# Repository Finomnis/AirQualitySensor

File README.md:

# AirQualitySensor

-- in development --

> **IMPORTANT**
>
> This project will most likely never be released in a way that it can be replicated by other makers.
> It is a repository for personal use only.
> 
> I kind of finished the project but didn't actually manufacture a dedicated PCB for it. Therefore there
> are no official schematics for the hardware.
>
> Note that the `v1` hardware that I did get manufactured had an unknown error in it that kept messing up the calibration of the Senseair S8 in random intervals. I never found out what the problem was.

---

Simple Air Quality sensor based on:

-   nRF52840 (Microcontroller + Zigbee)
-   Senseair S8 (CO2)
-   AM2302/DHT22 (Temperature + Humidity)
-   Zigbee (SmartHome Connectivity)
-   DOGM132W-5 (Display)
-   uGFX (UI)

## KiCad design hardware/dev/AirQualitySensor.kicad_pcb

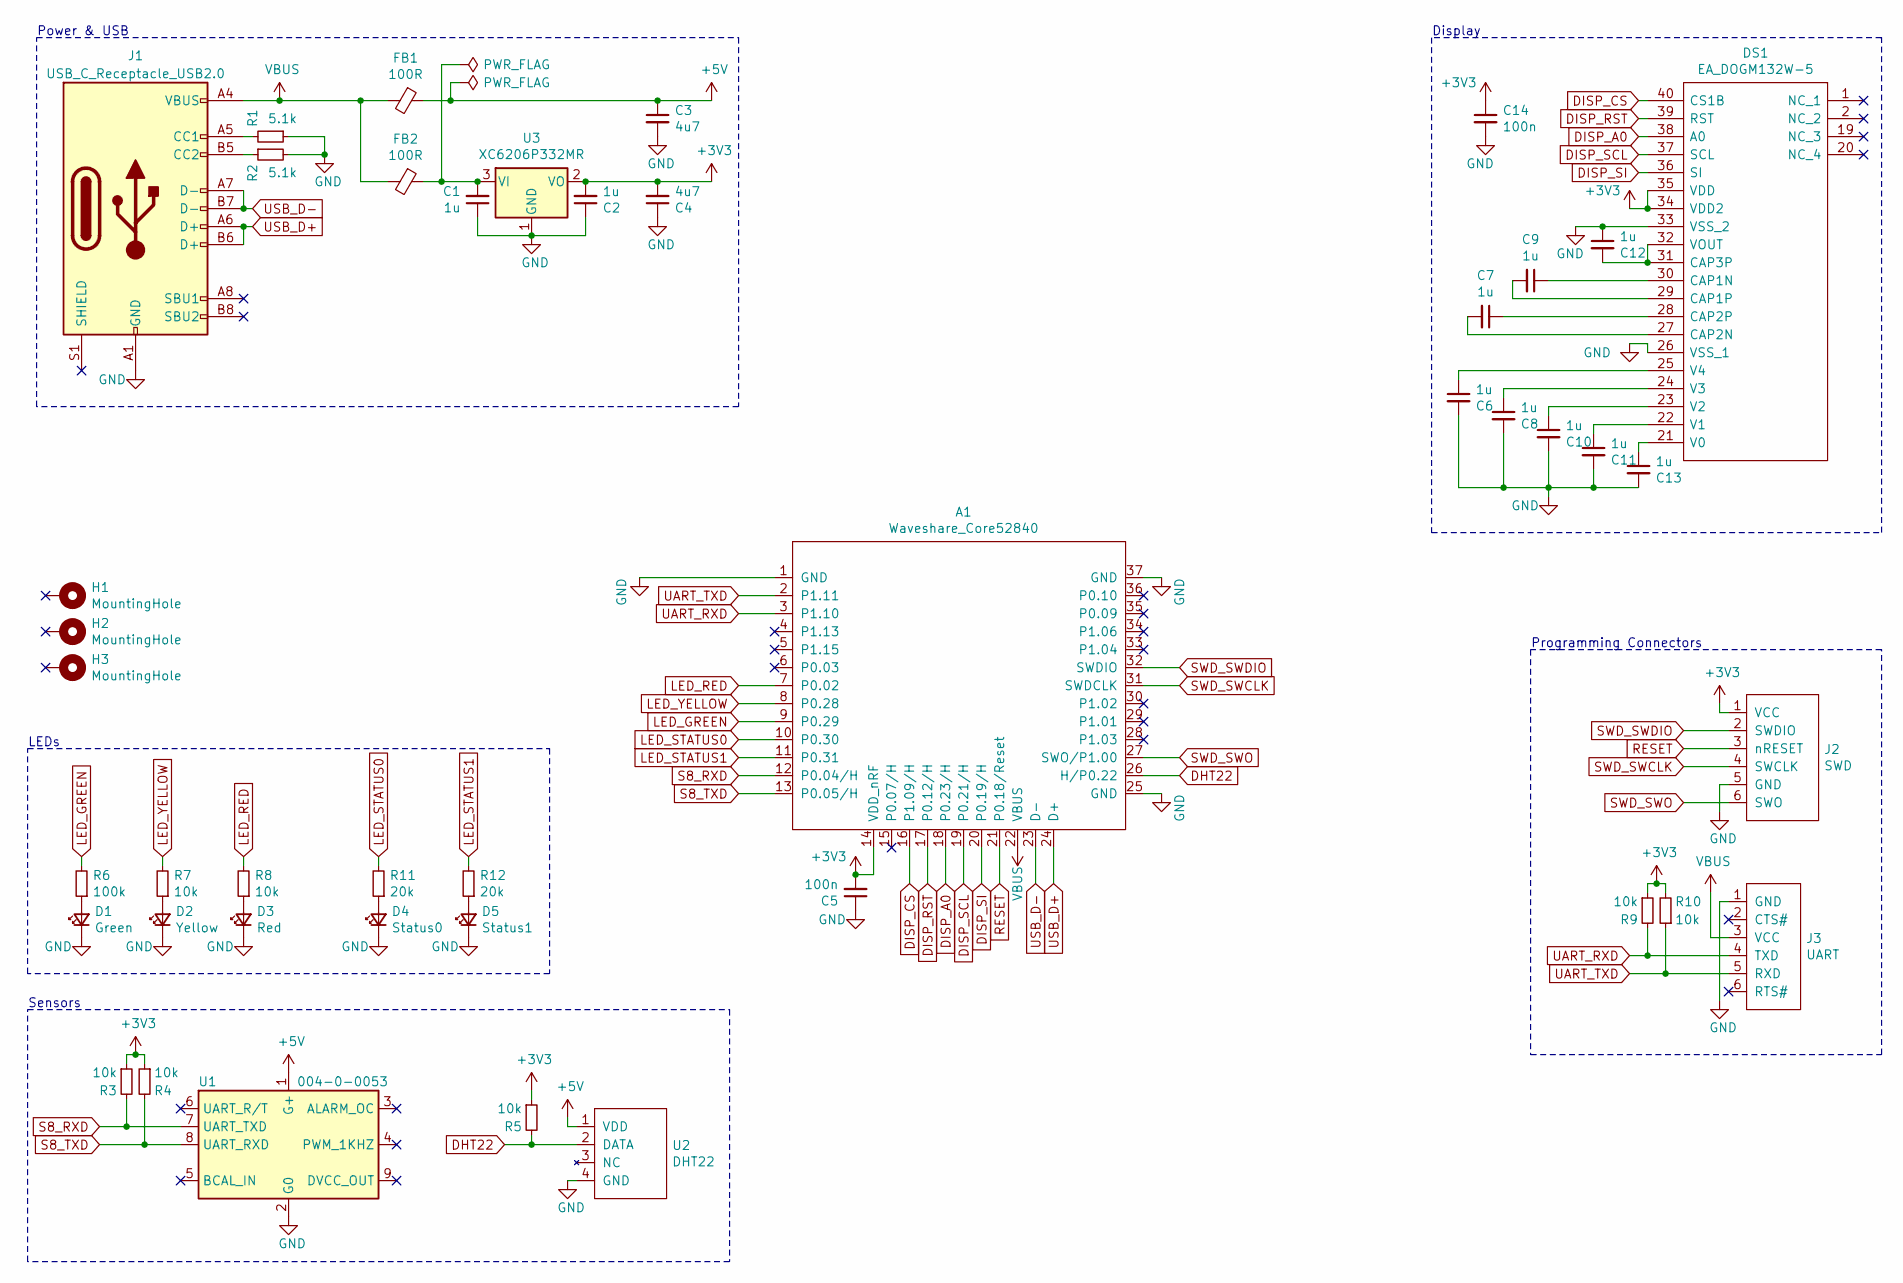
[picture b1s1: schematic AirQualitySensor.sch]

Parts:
A1: Waveshare_Core52840
C1, C2: 1u; C_0603_1608Metric
C3, C4: 4u7; C_0603_1608Metric
C5, C14: 100n; C_0402_1005Metric
C6, C7, C8, C9, C10, C11, C12, C13: 1u; C_0402_1005Metric
D1: Green; LED_D3.0mm
D2: Yellow; LED_D3.0mm
D3: Red; LED_D3.0mm
D4: Status0; LED_0805_2012Metric
D5: Status1; LED_0805_2012Metric
DS1: EA_DOGM132W-5; Mouser Part Number 790-EADOGM132W5
FB1, FB2: 100R; L_0805_2012Metric_Pad1.15x1.40mm_HandSolder
H1, H2, H3: MountingHole; MountingHole_2.5mm_Pad
J1: USB_C_Receptacle_USB2.0; USB_C_Receptacle_HRO_TYPE-C-31-M-12
J2: SWD; TC2030-IDC-FP
J3: UART; PinHeader_1x06_P2.54mm_Vertical
R1, R2: 5.1k; R_0402_1005Metric
R3, R4, R5, R7, R8, R9, R10: 10k; R_0402_1005Metric
R6: 100k; R_0402_1005Metric
R11, R12: 20k; R_0402_1005Metric
U1: 004-0-0053; Senseair_S8_Up
U2: DHT22
U3: XC6206P332MR; SOT-23

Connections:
+3V3: A1.14 (VDD_nRF), C2.2, C4.2, C5.2, C14.1, DS1.34 (VDD2), DS1.35 (VDD), J2.1 (VCC), R3.1, R4.1, R5.1, R9.1, R10.2, U3.2 (VO)
+5V: C3.1, FB1.1, U1.1 (G+), U2.1 (VDD)
DHT22: A1.26 (H/P0.22), R5.2, U2.2 (DATA)
DISP_A0: A1.18 (P0.23/H), DS1.38 (A0)
DISP_CS: A1.16 (P1.09/H), DS1.40 (CS1B)
DISP_RST: A1.17 (P0.12/H), DS1.39 (RST)
DISP_SCL: A1.19 (P0.21/H), DS1.37 (SCL)
DISP_SI: A1.20 (P0.19/H), DS1.36 (SI)
GND: A1.1 (GND), A1.25 (GND), A1.37 (GND), C1.1, C2.1, C3.2, C4.1, C5.1, C6.2, C8.2, C10.2, C11.2, C12.1, C13.2, C14.2, D1.1 (K), D2.1 (K), D3.1 (K), D4.1 (K), D5.1 (K), DS1.26 (VSS_1), DS1.33 (VSS_2), J1.A1 (GND), J1.A12 (GND), J1.B1 (GND), J1.B12 (GND), J2.5 (GND), J3.1 (GND), R1.1, R2.2, U1.2 (G0), U2.4 (GND), U3.1 (GND)
LED_GREEN: A1.9 (P0.29), R6.2
LED_RED: A1.7 (P0.02), R8.2
LED_STATUS0: A1.10 (P0.30), R11.2
LED_STATUS1: A1.11 (P0.31), R12.2
LED_YELLOW: A1.8 (P0.28), R7.2
unnamed: C1.2, FB2.1, U3.3 (VI)
unnamed: C6.1, DS1.25 (V4)
unnamed: C7.1, DS1.28 (CAP2P)
unnamed: C7.2, DS1.27 (CAP2N)
unnamed: C8.1, DS1.24 (V3)
unnamed: C9.1, DS1.30 (CAP1N)
unnamed: C9.2, DS1.29 (CAP1P)
unnamed: C10.1, DS1.23 (V2)
unnamed: C11.1, DS1.22 (V1)
unnamed: C12.2, DS1.31 (CAP3P), DS1.32 (VOUT)
unnamed: C13.1, DS1.21 (V0)
unnamed: D1.2 (A), R6.1
unnamed: D2.2 (A), R7.1
unnamed: D3.2 (A), R8.1
unnamed: D4.2 (A), R11.1
unnamed: D5.2 (A), R12.1
unnamed: J1.A5 (CC1), R1.2
unnamed: J1.B5 (CC2), R2.1
RESET: A1.21 (P0.18/Reset), J2.3 (nRESET)
S8_RXD: A1.12 (P0.04/H), R3.2, U1.7 (UART_TXD)
S8_TXD: A1.13 (P0.05/H), R4.2, U1.8 (UART_RXD)
SWD_SWCLK: A1.31 (SWDCLK), J2.4 (SWCLK)
SWD_SWDIO: A1.32 (SWDIO), J2.2 (SWDIO)
SWD_SWO: A1.27 (SWO/P1.00), J2.6 (SWO)
UART_RXD: A1.3 (P1.10), J3.4 (TXD), R9.2
UART_TXD: A1.2 (P1.11), J3.5 (RXD), R10.1
USB_D+: A1.24 (D+), J1.A6 (D+), J1.B6 (D+)
USB_D-: A1.23 (D-), J1.A7 (D-), J1.B7 (D-)
VBUS: A1.22 (VBUS), FB1.2, FB2.2, J1.A4 (VBUS), J1.A9 (VBUS), J1.B4 (VBUS), J1.B9 (VBUS), J3.3 (VCC)

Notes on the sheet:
Programming Connectors
Sensors
Power & USB
Display
LEDs

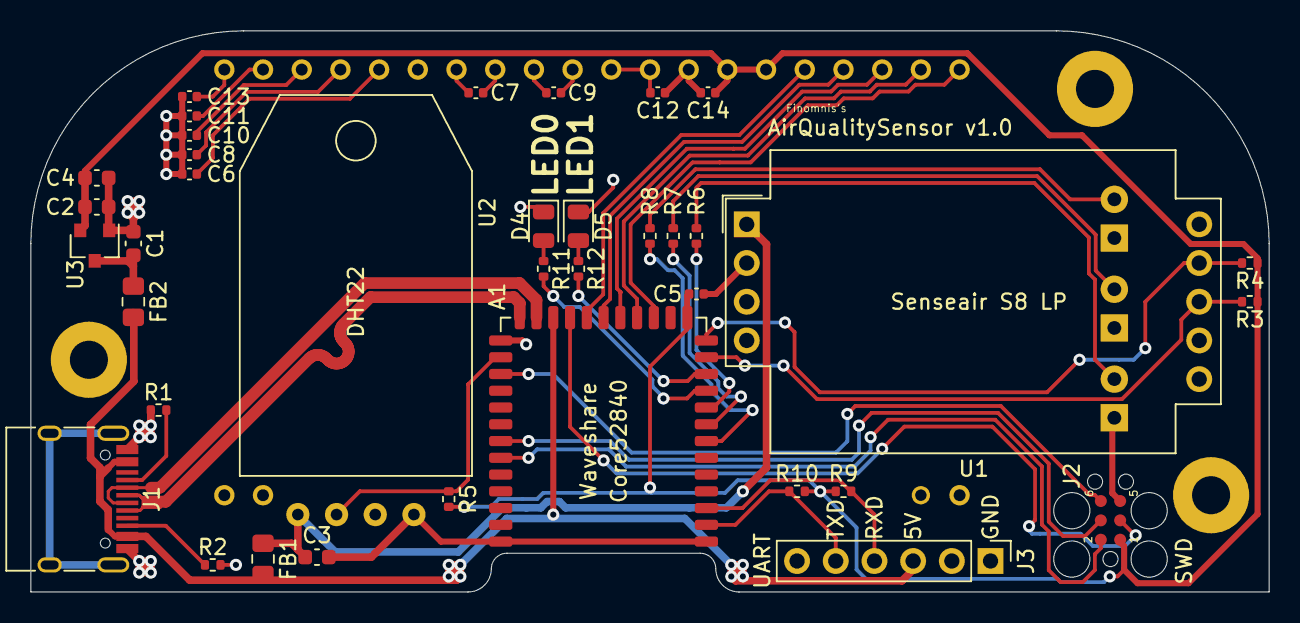
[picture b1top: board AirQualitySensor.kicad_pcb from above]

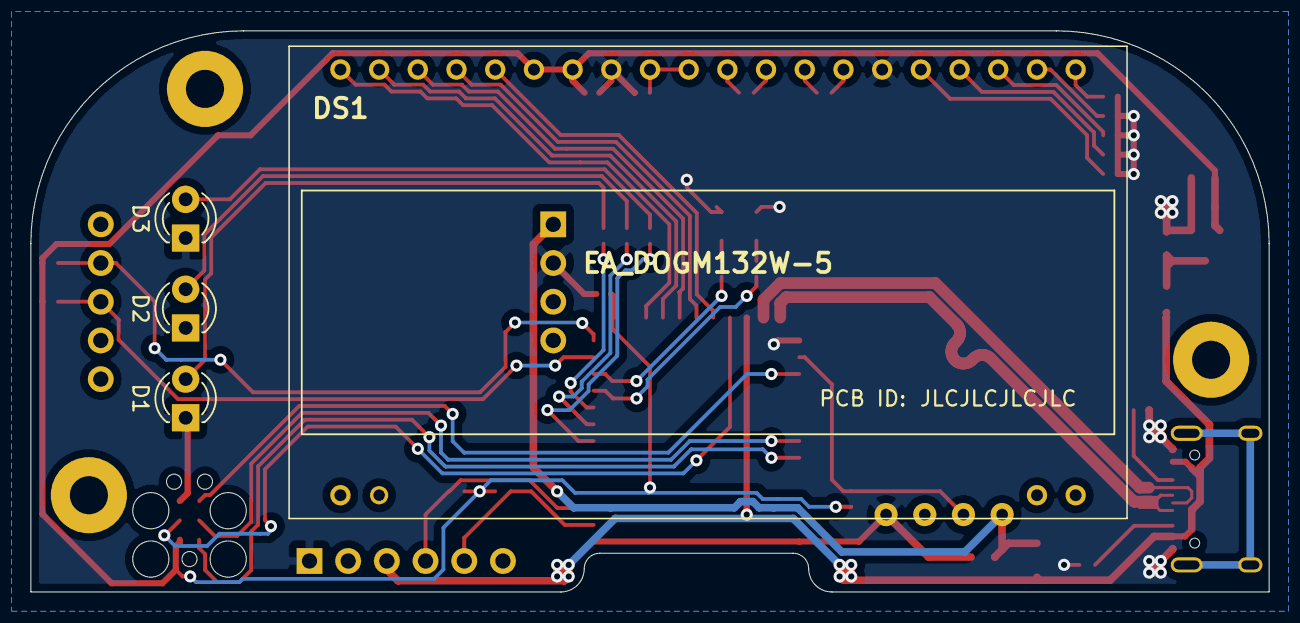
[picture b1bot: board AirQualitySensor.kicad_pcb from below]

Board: 2 copper layers, 81.3 x 36.8 mm, 44 parts (4 on the bottom side), 43 nets.

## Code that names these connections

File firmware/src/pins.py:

DHT22 = 32

LED_GREEN = 2
LED_YELLOW = 0
LED_RED = 4

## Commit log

2021-04-09 Add status LEDs
2021-04-09 Adjust humidity warning up to 55%
2021-04-10 Make AM2302 sensor a class and add second sensor
2021-04-10 Add LED state 'excellent'
2021-05-08 Intermediate commit
2021-05-08 Finished S8LP basic functionality
2021-05-08 Add S8 background calibration routine
2021-05-08 Disable calibration routine by default. Add CO2 thresholds.
2021-05-08 Reduce CO2 excellent value to less than 600ppm
2021-05-08 Reduce CO2 weak warning to 950 ppm
2021-05-09 Disable second AM2302
2021-05-09 Add CO2 sensor calibration over homie
2021-05-09 Set CO2 limits to 1000/1450
2021-05-09 Update LEDs even if homie is not connected
2021-05-09 Enable led on pin 0
2021-05-15 fix typo
2021-05-15 Remove AM2302_2 from pinout
2021-05-15 Add upload script for data
2021-05-15 Skip S8 sensor data reading if not connected
2021-05-15 Minor verbosity improvement
2021-05-16 Fix UART usage
    - Move all logging to Homie.getLogger()
    - Fix incorrect usage of Serial1 in S8LP
2021-05-16 Add ESP32 compatibility
2021-05-18 Move string constants to data section
2021-05-18 Fix ESP8266 pinout for alternate UART0
2021-05-18 Minor beautification in config.json
2021-05-19 Expose sensor values to class interfaces
2021-05-19 Move AM2302 pin to 14, remove LED pins
2021-05-19 Add status display (proof of concept, not pretty yet)
2021-05-19 Beautify display, add fonts
2021-05-19 Add degree symbol
2021-05-21 Add Neopixels. Currently displaying rainbow, not functional yet
2021-05-21 Make LEDs functional
2021-05-21 Disable H20 excellent state
2021-05-21 Adjustment of LED colors
2021-05-21 Fix homie include inconsistency
2021-05-21 Adjust LED colors
2021-05-21 Add connection state subsystem
2021-05-21 More color adjustements
2021-05-21 Bootstrap rpc class, implement request sending
2021-05-21 First working version of modbus rpc
2021-05-21 Minor rewrite of receive, add timeout, integrate sensor, cleanup
2021-05-21 Remove calibration routine of S8LP
2021-05-22 Temporary commit. Seems like code is getting worse, solution might almost be to stick to the previous version
2021-05-22 Reduce S8LP timeout to 100 ms
2021-05-22 Disable S8 calibration over MQTT by default
2021-06-01 Reduce LED brightness
2021-06-10 Remove platformio files and update README.md
2021-06-10 Bootstrap micropython
2021-06-10 Cleanup .gitignore
2021-06-10 Add homie library
2021-06-10 Add settings.py.example
2021-06-10 Add autocompletion for lib/
2021-06-10 Bootstrap Homie device
2021-06-11 Add protocol information to README
2021-06-11 Add microhomie version to README
2021-06-11 Add DHT22 sensor
2021-06-11 Rename am2302 to dht22
2021-06-11 Only update homie data if homie is connected
2021-06-11 Removed whitespace
2021-06-11 Add SensairS8 sensor
2021-06-11 Add stats extensions
2021-06-12 Remove data/ folder
2021-06-27 Add EInk pins
2021-06-27 Rename sensors directory to modules
2021-06-27 Add Waveshare 15.4 inch Eink display module
2021-06-27 More fixes to e-paper
2021-06-27 Remove EInk display code. EInk does not work reliably enough.
2021-06-27 Add CO2 listener mechanism
2021-06-27 Add status LEDs based on CO2 value
2021-06-28 Change error leds from blinking red to blinking all
    Blinking red was mistaken for 'bad CO2 value' several times.
2021-06-28 Move yellow to pin 15, as pin 0 seems to not be high impedance on standby
2021-07-18 Move firmware to firmware_micropython. Initialize platformio firmware/
2021-07-18 Add support for display DOGM132
2021-07-18 Update utils
2021-07-18 Hide display type in cpp file
2021-07-18 Add homie-cpp
2021-07-18 Remove homie-cpp library, as it is not compatible with MCUs
2021-07-18 Add custom Homie implementation
2021-07-19 Inverted order of device id
2021-07-19 Reduce verbosity
2021-07-19 Make HomieDevice nonmovable and noncopyable
2021-07-19 Add S8LP
2021-07-22 Rework Sensor structure + pinouts
2021-07-22 Add LEDs
2021-07-22 Add display initialization
2021-07-22 Add display content
2021-07-22 Remove micropython firmware, update README
2021-07-22 Adjust display content, add start screen
2021-07-22 Minor display content fix
2021-07-22 Move SensorError and Startup to their own classes
2021-08-15 Move firmware to firmware_platformio
2021-08-15 Add zephyr sample
2021-08-15 Add more sample code
2021-08-15 Add .vscode config files
2021-08-16 Add loading of NRF sdk to terminal
2021-08-16 Get Feather + RTT working
2021-08-16 Remove obsolete boards
2021-09-01 Add C/C++/CMake VSCode config
2021-09-02 Add CMake as intellisense provider
2021-09-04 Add zigbee basic skeleton
2021-09-05 Imitate to be a TPZRCO2HT-Z3
2021-09-05 Make custon descriptors, add humidity sensor cluster
2021-09-06 Disable RTT debugging
2021-09-06 Add temperature reporting
2021-09-10 Add publish_temperature function
2021-09-17 Change Zigbee id to Finomnis - AirQualitySensor-1
2021-09-17 Add humidity reporting
2021-09-17 Add co2 cluster
2021-09-17 Add CO2 reporting
2021-09-17 Convert co2 value type to float
2021-09-17 Cleanup non-needed code
2021-09-17 Fix order of zigbee registration functions
2021-09-18 Move zigbee initialization code to separate file
2021-09-18 Add DHT22 sensor to devicetree
2021-09-18 Implement dht22 sensor sampling
2021-09-18 Move DHT22 code to subsys
2021-09-18 Initialize dht22 thread statically
2021-09-18 Add subscription model for DHT22 values
2021-09-18 Remove obsolete include
2021-09-18 Connect DHT22 values to zigbee device
2021-09-21 Make dht22 stack size even
2021-09-21 Move zigbee device to subfolder, implement custom main loop
2021-09-21 Start rework for zigbee value publishing mechanism
2021-09-21 Minor rework in value publishing
2021-09-22 Actually publish values to zigbee
2021-09-22 Add missing statics
2021-09-22 Slow down debug led again
2021-09-22 Remove obsolete debug message
2021-10-01 Move subsys to modules directory
2021-10-01 Move DHT22 Kconfig to SUBSYS_DHT22
2021-10-01 Move zigbee_device to subsys folder
2021-10-01 Add Sensair S8 driver skeleton
2021-10-02 Add CO2 sensor to device tree and enable driver (skeleton)
2021-10-02 Remove obsolete sample.yaml
2021-10-02 Refactor Kconfig menuconfig
2021-10-02 Reference dht22 sensor by device tree path
2021-10-02 Add sensair s8 sensor driver skeleton
2021-10-02 Add modbus initialization to sensair s8
2021-10-02 Add missing MODBUS_ROLE_CLIENT to Kconfig of sensair_s8
2021-10-02 Add sensair s8 sensor id retreival
2021-10-02 Add sensor type check to sensair_s8 init function
2021-10-02 Fix sensor sample formatting in main
2021-10-02 Implement sensair_s8 sample fetching
2021-10-02 Add senseair s8 sampling subsystem
2021-10-02 Rename sensair to senseair (fix typo)
2021-10-03 Publish CO2 value to Zigbee
2021-10-03 Fix subsys thread priorities
2021-10-03 Bootstrap CO2 LEDs subsystem
2021-10-03 Add CO2 LEDs to device tree
2021-10-03 Implement blink logic of CO2 LEDs
2021-10-04 Fix co2 leds device tree
2021-10-04 Flip main and zigbee priority
2021-10-04 Disable LED blinking in main
2021-10-04 Control LED pins from co2_leds module
2021-10-04 Retry data fetching if DHT22 read fails
2021-10-04 Fix retry for DHT22 samples
2021-10-04 Minor beautification
2021-10-05 Bootstrap Kicad files
2021-10-05 Remove light_bulb zephyr example
2021-10-05 Add Kicad symbols library
2021-10-06 Add Waveshare Core52840 Symbol
2021-10-06 Add datasheet to nrf52840
2021-10-06 Add Waveshare Core52840 Footprint
2021-10-06 Minor fixes in Core52840 footprint
2021-10-06 Link symbol and footprint for Core52840
2021-10-06 Start schematic
2021-10-06 Add EA DOGM132W-5 part
2021-10-06 Minor beautification in DOGM footprint
2021-10-06 Add Senseair S8
2021-10-06 Add DHT22 model
2021-10-06 Add Sensair S8 down model
2021-10-06 Add Sensair S8 up model
2021-10-06 Minor beautifications
2021-10-08 More Layout work
2021-10-08 Add TC2030 connector
2021-10-08 Add UART connector
2021-10-08 Continue schematic
2021-10-08 More layouting
2021-10-08 Finish first layout
2021-10-09 Move sensor pins to high drive output pins
2021-10-09 Increase clearing between display and screw hole
2021-10-09 Add PCB Name and manufacturer ID
2021-10-09 Minor fix
2021-10-09 Minor fixes
2021-10-09 Add v1 gerber files
2021-10-09 Fix 100n capacitor values typo
2021-10-09 Fix ferrite bead having wrong footprint
2021-10-09 Update gerber files
2021-10-09 Add BOM and preliminary pick-and-place file
2021-10-09 Fix Status1 LED typo
2021-10-09 Fix component orientation
2021-10-09 Add schematic pdf; minor beautification in schematic
2021-10-09 Finalize v1 hardware, duplicate files to dev folder
2021-10-10 Fix inductor footprint
2021-10-29 Fix flipped red-green LEDs
2021-10-29 Fix clearance issue
2021-10-29 Create LICENSE
2021-10-29 Add airqualitysensor_v1 board
2021-10-29 Port over missing device tree entries and fix indents
2021-10-29 Fix board definition location and naming
2021-10-29 Switch CMake board to aqs-v1
2021-10-29 Fix LEDs in device tree and partially rewrite co2_leds to use DT api
2021-10-29 Add zigbee2mqtt configuration
    Just temporal. Once the device is finished, it will be added to
    zigbee2mqtt itself.
2021-11-05 Remove Shell, add RTT logging
    Reason: AirQualitySensor v1 hardware has a collision between JTAG
    programming port and UART (which has to be fixed in future revisions)
    which prevents UART from bein used properly. Therefore use RTT instead.
    (UART was used because UART connections survive flash/reset, which RTT
    does not)
2021-11-05 Remove incorrect README from firmware
2021-11-05 Fix prj.conf warning
2021-11-05 Add skeleton for DOGM132 display
2021-11-05 Add uGFX external library
2021-11-06 Use explicit error parameter in CO2 callbacks
2021-11-06 Remove CO2 min/max attributes, publish 'NaN' as error value
2021-11-06 Handle negative CO2 measurements from S8 correctly
2021-11-07 Fix modbus not working
    For some reason, enabling RTT causes the S8 Modbus connection to stop
    working.
    Needs further investigation in future.
2021-11-07 Fix LEDs handling negative CO2 concentration incorrectly
2022-01-21 Add galvanometer knowledge
2022-01-21 Add galvo test firmware
2022-01-22 Finish galvo test firmware
2022-01-22 Add knowledge
2022-01-23 Remove ncs firmware
2022-01-23 Move rust firmware to firmware_rust folder
2022-01-23 Add sensor scd4 module and serial number reading
2022-01-23 Implement self test for scd4x
2022-01-23 Minor refactoring. Schedule sensor ticks after self test
2022-01-23 Rewrite using the delay function. Implement sensor reading
2022-01-23 Minor refactoring
2022-01-23 Add measurement conversions
2022-01-30 More work on rust firmware. Add subsystems and watchdog
2022-01-30 Implement LEDs
2022-02-01 Add more galvos to galvotest
2022-02-01 Implement galvo control loop
2022-02-01 More work on galvos
2022-02-01 Implement galvo display
2022-02-05 Minor refactoring on scd4x controller code
2022-02-05 Add calibration data for my sensor
2022-02-06 Adjust temperature offset
2022-03-01 Remove temperature offset from scd4x sensor
2022-09-13 Update versions
2022-09-13 Update CO2 ranges to new 2500 scale
2022-09-13 Fix version update error
2022-09-20 Add v1 rust firmware
2022-09-20 Fix error handling in v1 firmware
2022-09-21 Simplify IOPin
2022-09-28 Remove custom IOPin implementation as it was merged upstream
2023-01-20 Add blinking red at max CO2
